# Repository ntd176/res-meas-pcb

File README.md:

# res-meas-pcb

Measurement: Unbalanced wheatstone bridge with ads1115 (16-bit ADC)

Monitoring: Real time web interface using websocket

Hardware Design: Kicad (Schematic & PCB Layout)

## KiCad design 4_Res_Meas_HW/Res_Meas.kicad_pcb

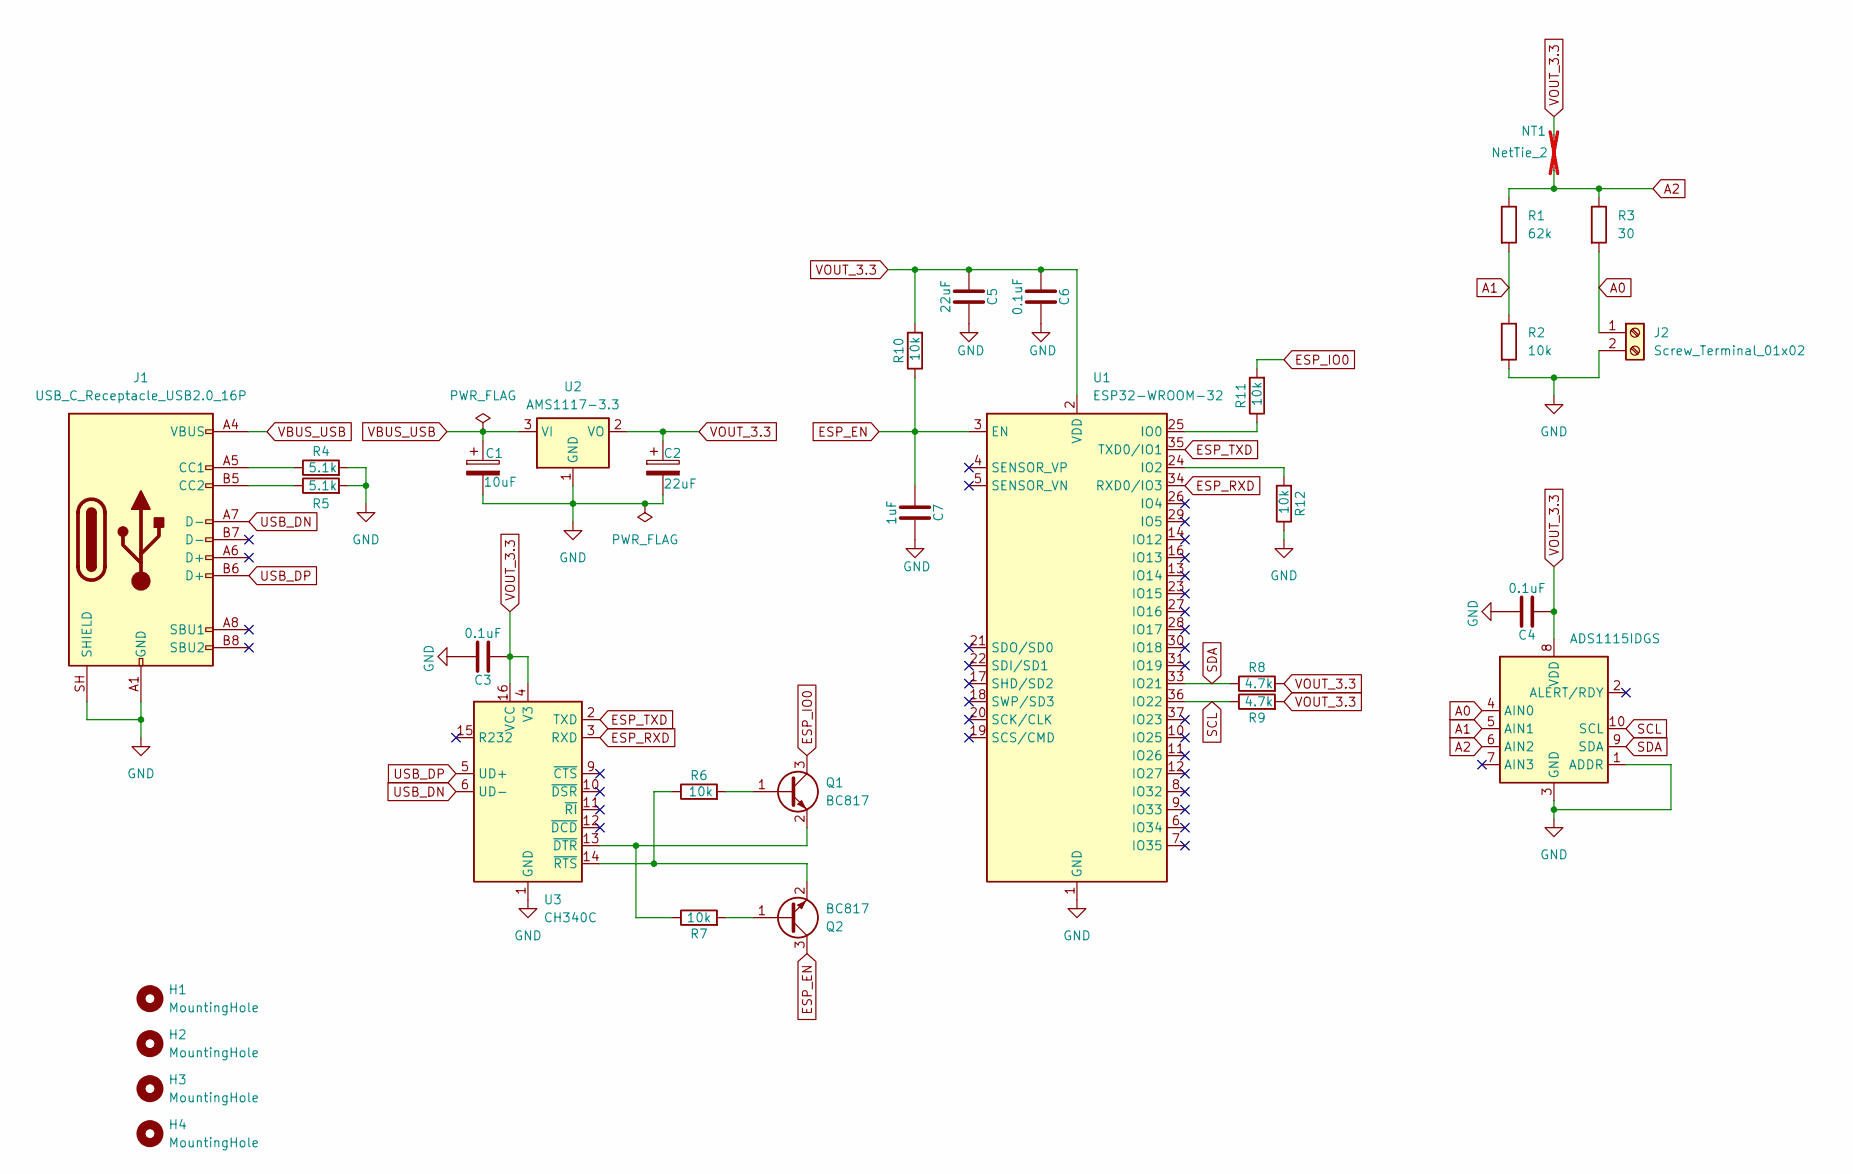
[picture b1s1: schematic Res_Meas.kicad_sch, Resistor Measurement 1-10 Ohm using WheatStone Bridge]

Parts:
C1: 10uF; CP_EIA-7343-31_Kemet-D_HandSolder
C2: 22uF; CP_EIA-7343-31_Kemet-D_HandSolder
C3, C4, C6: 0.1uF; C_0805_2012Metric
C5: 22uF; C_0805_2012Metric
C7: 1uF; C_0805_2012Metric
H1, H2, H3, H4: MountingHole; MountingHole_3.2mm_M3
J1: USB_C_Receptacle_USB2.0_16P; USB_C_Receptacle_GCT_USB4105-xx-A_16P_TopMnt_Horizontal
J2: Screw_Terminal_01x02; PinHeader_1x02_P2.54mm_Vertical
NT1: NetTie_2; NetTie-2_SMD_Pad0.5mm; not fitted
Q1, Q2: BC817; SOT-23
R1: 62k; R_Axial_DIN0411_L9.9mm_D3.6mm_P15.24mm_Horizontal
R2: 10k; R_Axial_DIN0411_L9.9mm_D3.6mm_P15.24mm_Horizontal
R3: 30; R_Axial_DIN0411_L9.9mm_D3.6mm_P15.24mm_Horizontal
R4, R5: 5.1k; R_0805_2012Metric
R6, R7, R10, R11, R12: 10k; R_0805_2012Metric
R8, R9: 4.7k; R_0805_2012Metric
U1: ESP32-WROOM-32; ESP32-WROOM-32E
U2: AMS1117-3.3; SOT-223-3_TabPin2
U3: CH340C; SOIC-16_3.9x9.9mm_P1.27mm
U5: ADS1115IDGS; TSSOP-10_3x3mm_P0.5mm

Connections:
A0: J2.1, R3.2, U5.4 (AIN0)
A1: R1.2, R2.1, U5.5 (AIN1)
A2: NT1.1, R1.1, R3.1, U5.6 (AIN2)
ESP_EN: C7.2, Q2.3 (C), R10.1, U1.3 (EN)
ESP_IO0: Q1.3 (C), R11.2
ESP_RXD: U1.34 (RXD0/IO3), U3.3 (RXD)
ESP_TXD: U1.35 (TXD0/IO1), U3.2 (TXD)
GND: C1.2, C2.2, C3.1, C4.1, C5.1, C6.1, C7.1, J1.A1 (GND), J1.A12 (GND), J1.B1 (GND), J1.B12 (GND), J1.SH (SHIELD), J2.2, R2.2, R4.2, R5.2, R12.1, U1.1 (GND), U1.15 (GND), U1.38 (GND), U1.39 (GND), U2.1 (GND), U3.1 (GND), U5.1 (ADDR), U5.3 (GND)
unnamed: J1.A5 (CC1), R4.1
unnamed: J1.B5 (CC2), R5.1
unnamed: Q1.1 (B), R6.2
unnamed: Q1.2 (E), R7.1, U3.13 (~DTR)
unnamed: Q2.1 (B), R7.2
unnamed: Q2.2 (E), R6.1, U3.14 (~RTS)
unnamed: R11.1, U1.25 (IO0)
unnamed: R12.2, U1.24 (IO2)
SCL: R9.1, U1.36 (IO22), U5.10 (SCL)
SDA: R8.1, U1.33 (IO21), U5.9 (SDA)
USB_DN: J1.A7 (D-), J1.B7 (D-), U3.6 (UD-)
USB_DP: J1.A6 (D+), J1.B6 (D+), U3.5 (UD+)
VBUS_USB: C1.1, J1.A4 (VBUS), J1.A9 (VBUS), J1.B4 (VBUS), J1.B9 (VBUS), U2.3 (VI)
VOUT_3.3: C2.1, C3.2, C4.2, C5.2, C6.2, NT1.2, R8.2, R9.2, R10.2, U1.2 (VDD), U2.2 (VO), U3.4 (V3), U3.16 (VCC), U5.8 (VDD)

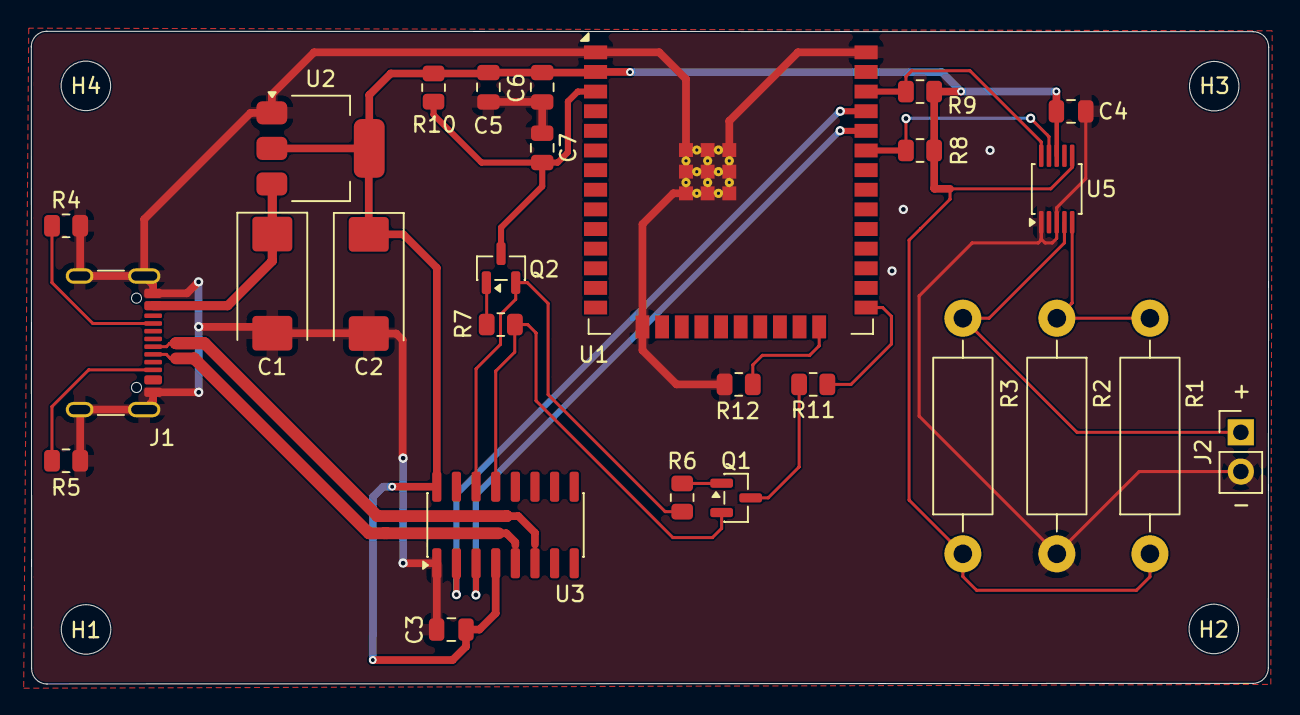
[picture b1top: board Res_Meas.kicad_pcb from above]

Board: 2 copper layers, 80.0 x 42.2 mm, 32 parts (0 on the bottom side), 22 nets.

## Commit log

2026-05-27 uploading_soldering_test_27/05/2026
2026-06-03 uploading_img
2026-06-06 uploading_block_diagram_and_result_VR_VS_LTspice
2026-06-08 upload_hw
2026-06-08 uploading_fw_v1
2026-06-08 uploading_pcb_testing
2026-06-08 uploading_refdoc
